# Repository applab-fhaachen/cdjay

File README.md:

# CDjay

## Introduction
The success of Pioneer's CDJ-Players is based on their usability and performance-oriented controls. And while the technology has evolved from CDs over SD-Cards to USB-Keys or direct interaction with a laptop, the control interface itself hasn't changed much. 
Modern CDJs, such as the CDJ-850, CDJ-900, CDJ-2000, and newer offer the possibility to directly connect to a host software, such as Algoriddim DJay, Native Instruments' Traktor, Serato Scratch, in order to be used as controller. 
The goal of this project is to bring this capability to older CDJ-Models in order to keep their control interface. 

## Related Work
A number of other projects have looked at the same idea. Some turning the CDJ into a MIDI-based controller, others integrating a RaspberryPi and running Mixxx, and open source DJ-Software on it, essentially turning them into full-blown, standalone, media-players. 

## About this repository
This repo holds the firmware that turns a Pioneer CDJ-850 into a class-compliant USB controller. It runs on a Raspberry Pi Pico 2 W wired into the CDJ's front-panel button matrix, and it currently:
- Scans the CDJ's S1-S5 / KD0-KD2 button matrix (the display controller drives the S lines; the Pico reads back which K lines go high on each line, see `notes.md` and `include/button/cdj_button.h`) and debounces/queues press-release edges.
- Translates button edges into standard USB-MIDI note on/off messages (`headers/midi_messages.h`) sent over TinyUSB, so any MIDI-capable host (e.g. djay on an iPad) sees the CDJ as a controller.
- Includes a USB-HID descriptor scaffold matching the CDJ-850's own vendor-defined report layout (see `pioneer-800 description.md`) for a future, richer bidirectional mode (LED feedback from the host), though report population is not yet wired up.
- Tracks rotary/jog encoder pulse timing (`include/button/encoder.c`) to derive a speed-scaled MIDI velocity for the search wheel.

Only the Play and Cue buttons are connected end-to-end today (`cdjay.c`); the remaining matrix positions are mapped in `midi_messages.h` but not yet instantiated.

### Hardware
- Raspberry Pi Pico 2 W (`PICO_BOARD pico2_w`), wired to the CDJ-850's S1-S5 (GPIO 10-14) and KD0-KD2 (GPIO 7-9) matrix lines.
- Wiring reference: `image.png` / `notes.md`.

### Building
Requires the Raspberry Pi Pico SDK (v2.2.0) and toolchain, e.g. via the [Pico VS Code extension](https://marketplace.visualstudio.com/items?itemName=raspberry-pi.raspberry-pi-pico) or a manual SDK install pointed to by `PICO_SDK_PATH`.

```sh
mkdir -p build && cd build
cmake ..
make -j4
```

Flash `build/cdjay.uf2` to the Pico by holding BOOTSEL while plugging it in, then copying the file to the mass-storage drive that appears.

### Status
Done:
- Button matrix scanning, debouncing, and edge-queueing (S1-S5 x KD0-KD2).
- USB-MIDI transport via TinyUSB, with a full note-message lookup table for every matrix cell.
- Play and Cue buttons wired end-to-end: press/release -> MIDI note on/off.
- Rotary/jog encoder pulse-interval tracking, mapped to a MIDI-velocity range.
- USB-HID report descriptor matching the real CDJ-850 vendor report layout (not yet populated with live data).

In progress / not yet wired up:
- Remaining buttons (Hold, Time, Track Back/Forward, Eject, Jet, Scratch Back/Forward, Menu/Tag, Zip, Wah) are mapped in `midi_messages.h` and commented out in `cdjay.c`, but not instantiated as `cdj_button_t`s.
- Search/jog encoder velocity is computed (`search_encoder_velocity()`) but not yet fed into a MIDI message.
- `hid_in_report` is never updated from button state, so the HID path currently only sends an all-zero report.
- `tud_hid_set_report_cb` has a TODO for driving the CDJ's own LEDs from host feedback (e.g. Play/Cue LED state from djay).

Roadmap:
1. Instantiate the remaining `create_cdj_button()` calls and confirm each maps to the correct MIDI note against a real CDJ-850.
2. Wire jog/search-wheel velocity into MIDI CC or note messages.
3. Populate `hid_in_report` from button state and enable the HID path as an alternative/parallel transport to MIDI.
4. Implement LED feedback from host HID output reports so the CDJ's own display/LEDs reflect deck state (playing, cued, etc.).
5. Validate end-to-end with djay on iPad (and ideally a second host, e.g. a MIDI-only DAW) for both transports.

## USB-HID
The key is the USB-HID protocol which the newer models provide. Instead of registering as a USB-Midi Device, they have their own, proprietary protocol. While this conflicts with the idea of an open and flexible interface, it has the advantage of providing bi-directional communication, and thus, be able to show additional information directly on the display of the CDJ. The most common DJ software supports the HID protocol.

### Details
Technically, the CDJ registers as a USB device with a number of endpoints:
- The USB-HID interface for the control messages.
- a USB-audio interface for audio-output from the CDJ itself (relevant if you don't use the internal mixer of the software, but an external mixer). 

## Interface
Since we want to focus on interfacing the old CDJs with the modern world (USB-C, Software, etc.), we use iPad mini running Algoriddim's djay in single deck mode, which gives us all the benefits such as touch interaction, integration to streaming services, etc.. Any iPad being able to run djay is fine, although interfacing is easier with the usb-c models. 

### Installation
Install djay from the App-Store on your iPad. Technically, it is possible to run djay from an iPhone, however, it doesn't support single-deck mode on smaller devices. 

### Connecting
If you have an iPad with a lightning-connector, you need a lightning to usb-converter that supports USB OTG. This will make the iPad the host of your USB connection, and the CDJay the client. 
For the USB-Models, just connect the USB-C connection to your iPad. 

## Acknowledgements

This project was supported by...

## License
MIT License

All trademarks are property of their respective owners. This project is part of the education at FH Aachen University of Applied Sciences and not affiliated to any of the brand names.

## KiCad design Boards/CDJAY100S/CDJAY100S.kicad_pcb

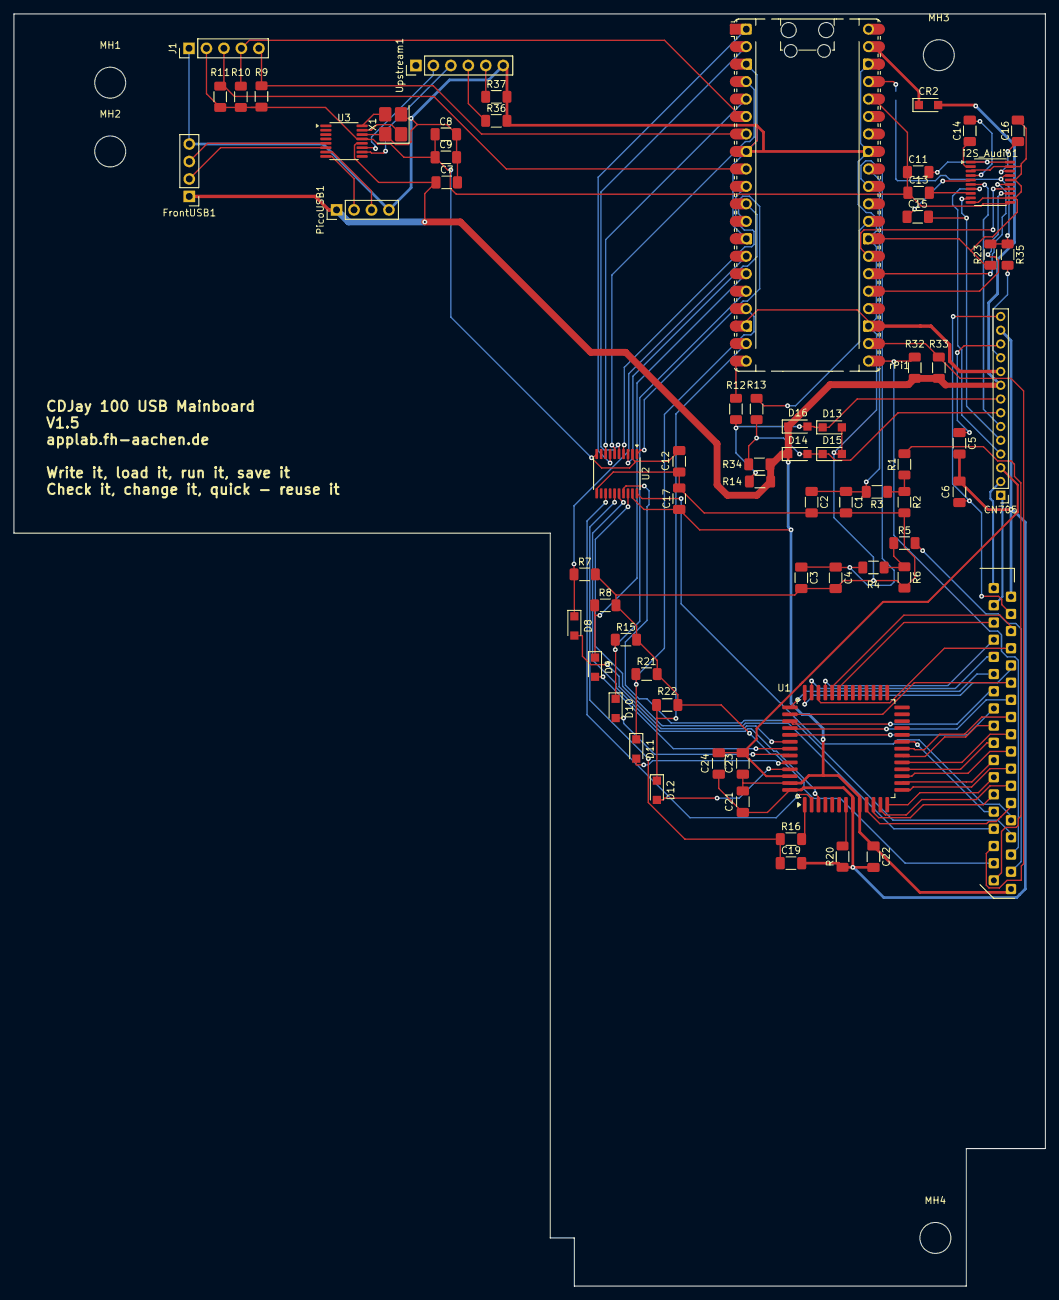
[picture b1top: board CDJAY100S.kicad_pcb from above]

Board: 2 copper layers, 150.0 x 185.0 mm, 74 parts (1 on the bottom side), 98 nets.

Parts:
C1, C4, C11, C12, C13, C17, C21, C22, C23, C24: 100 n; C_1206_3216Metric_Pad1.33x1.80mm_HandSolder
C2, C3: 10 u; C_1206_3216Metric_Pad1.33x1.80mm_HandSolder
C5, C6: 100 u; C_1206_3216Metric_Pad1.33x1.80mm_HandSolder
C7, C8: 10u; C_1206_3216Metric_Pad1.33x1.80mm_HandSolder
C9: 1uf; C_1206_3216Metric_Pad1.33x1.80mm_HandSolder
C14, C15: 2.2 u; C_1206_3216Metric_Pad1.33x1.80mm_HandSolder
C16: 1 u; C_1206_3216Metric_Pad1.33x1.80mm_HandSolder
C19: 100 p; C_1206_3216Metric_Pad1.33x1.80mm_HandSolder
CN701: 52492-3620; ConnectorFPC&FFC_MOL52045-3645-36P_1
CN705: 52151-1410; PinHeader_1x14_P2.00mm_Vertical
CR2: MBR120VLSFT1G; Nexperia_CFP3_SOD-123W
D8, D9, D10, D11, D12, D13, D14, D15, D16: 1SS355VM; Nexperia_CFP3_SOD-123W
FrontUSB1: Conn_01x04_Pin; PinHeader_1x04_P2.54mm_Vertical
J1: Rotary Encoder; PinHeader_1x05_P2.54mm_Vertical
JP1: SolderJumper-2_P1.3mm_Open_Pad1.0x1.5mm
MH1, MH2, MH3, MH4: MountingHole_4.5mm
PicoUSB1: Conn_01x04_Pin; PinHeader_1x04_P2.54mm_Vertical
R1, R5, R9, R10, R11: 10 k; R_1206_3216Metric_Pad1.30x1.75mm_HandSolder
R2, R6: 20 k; R_1206_3216Metric_Pad1.30x1.75mm_HandSolder
R3, R4, R36, R37: 5.1 k; R_1206_3216Metric_Pad1.30x1.75mm_HandSolder
R7, R8, R14, R15, R21, R22, R32, R33, R34, R35: 10k; R_1206_3216Metric_Pad1.30x1.75mm_HandSolder
R12, R13: 2k; R_1206_3216Metric_Pad1.30x1.75mm_HandSolder
R16: 1 k; R_1206_3216Metric_Pad1.30x1.75mm_HandSolder
R20: 82 k; R_1206_3216Metric_Pad1.30x1.75mm_HandSolder
R23: 20k; R_1206_3216Metric_Pad1.30x1.75mm_HandSolder
U1: PT6324Q; QFP-52_14x14mm_P1mm_1
U2: TXS0108EPW; TSSOP-20_4.4x6.5mm_P0.65mm
U3: CH334R; QSOP-16_3.9x4.9mm_P0.635mm
Upstream1: Conn_01x06_Pin; PinHeader_1x06_P2.54mm_Vertical
X1: 12MHz; Crystal_SMD_3225-4Pin_3.2x2.5mm_HandSoldering
i2S_Audio1: PCM5102; TSSOP-20_4.4x6.5mm_P0.65mm
rPi1: RaspberryPi_Pico; RaspberryPi_Pico_Common_Unspecified

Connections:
+3V3: C8.1, C9.1, C11.1, C12.1, C13.1, J1.2 (+), R9.2, R10.1, R11.1, U2.2 (VCCA), U2.10 (OE), U3.13 (VDD33_{LDO}), i2S_Audio1.11 (FLT), rPi1.36 (3V3)
+5V: C7.1, C17.1, C21.1, C22.1, C23.2, CN701.1 (V+5V), CN705.9 (V+5V), CR2.2, D14.1 (K), D16.1 (K), FrontUSB1.1 (VBUS), PicoUSB1.1 (VBUS), R14.2, R32.2, R33.2, R34.2, U1.9 (VDD), U1.51 (VDD), U2.19 (VCCB), U3.12 (V5)
/ADIN: C3.1, C4.1, R4.2, rPi1.31 (GPIO26_ADC0)
/CLK: C19.1, R16.1, U2.15 (B5)
/CT: C1.1, C2.1, R3.2, rPi1.32 (GPIO27_ADC1)
/DIN: U1.2 (DIN), U2.13 (B7)
/JOG1: CN701.5 (JOG1), R32.1, rPi1.21 (GPIO16)
/JOG2: CN701.6 (JOG2), R33.1, rPi1.22 (GPIO17)
/KD0: CN701.9 (KD0), U2.20 (B1)
/SPI0 CS: U2.5 (A4), rPi1.2 (GPIO1)
/SPI0 RX: U2.7 (A6), rPi1.1 (GPIO0)
/SPI0 SCK: U2.6 (A5), rPi1.4 (GPIO2)
/SPI0 TX: U2.8 (A7), rPi1.5 (GPIO3)
/STB: U1.3 (STB), U2.16 (B4)
GND: C1.2, C2.2, C3.2, C4.2, C7.2, C8.2, C9.2, C12.2, C16.2, C17.2, CN701.4 (GNDD), CN705.10 (GNDD), D13.2 (A), D15.2 (A), FrontUSB1.4 (GND), J1.1 (GND), PicoUSB1.4 (GND), R2.2, R6.2, R7.2, R8.2, R15.2, R21.2, R22.1, R23.1, R36.2, R37.2, U2.11 (GND), U3.14 (GND), Upstream1.6 (GND), X1.2 (G), X1.4 (G), i2S_Audio1.3 (CPGND), i2S_Audio1.10 (DEMP), i2S_Audio1.12 (SCK), i2S_Audio1.16 (FMT), i2S_Audio1.19 (DGND), rPi1.3 (GND), rPi1.8 (GND), rPi1.13 (GND), rPi1.18 (GND), rPi1.23 (GND), rPi1.28 (GND), rPi1.33 (AGND), rPi1.38 (GND)
GNDA: C15.2, CN705.5 (GNDA), i2S_Audio1.9 (AGND)
GNDS: C5.2, C6.1, C19.2, C21.2, C22.2, C24.2, CN701.35 (GNDS), CN705.13 (GNDS), R20.1, U1.8 (GND), U1.52 (GND)
unnamed: CN701.36 (AC1), CN705.2 (AC1)
unnamed: CN701.34 (AC2), CN705.1 (AC2)
unnamed: CN701.2 (ADIN), R1.2
unnamed: CN701.3 (CT), R5.2
unnamed: CN701.32 (G1), U1.34 (GR1)
unnamed: CN701.31 (G2), U1.35 (GR2)
unnamed: CN701.30 (G3), U1.36 (GR3)
unnamed: CN701.29 (G4), U1.37 (GR4)
unnamed: CN701.28 (G5), U1.38 (GR5)
unnamed: CN701.27 (G6), U1.39 (GR6)
unnamed: CN701.26 (G7), U1.40 (GR7)
unnamed: CN701.25 (G8), U1.41 (GR8)
unnamed: CN701.24 (G9), U1.42 (GR9)
unnamed: CN701.23 (G10), U1.43 (GR10)
unnamed: CN701.22 (G11), U1.44 (GR11)
unnamed: CN701.8 (KD1), U2.18 (B2)
unnamed: CN701.7 (KD2), U2.17 (B3)
unnamed: CN701.11 (S1), U1.10 (SG1)
unnamed: CN701.12 (S2), U1.11 (SG2)
unnamed: CN701.13 (S3), U1.12 (SG3)
unnamed: CN701.14 (S4), U1.13 (SG4)
unnamed: CN701.15 (S5), U1.14 (SG5)
unnamed: CN701.16 (S6), U1.15 (SG6)
unnamed: CN701.17 (S7), U1.16 (SG7)
unnamed: CN701.18 (S8), U1.17 (SG8)
unnamed: CN701.19 (S9), U1.18 (SG9)
unnamed: CN701.20 (S10), U1.19 (SG10)
unnamed: CN701.21 (S11), U1.20 (SG11)
unnamed: CN701.10 (S12), U1.21 (SG12)
unnamed: CN705.6 (AUDIO_L), i2S_Audio1.6 (OUTL)
unnamed: CN705.4 (AUDIO_R), i2S_Audio1.7 (OUTR)
unnamed: CN705.8 (CONT1), D13.1 (K), D16.2 (A), R12.2, R14.1
unnamed: CN705.7 (CONT2), D14.2 (A), D15.1 (K), R13.2, R34.1
unnamed: CN705.11 (/RST), R35.2
unnamed: D8.2 (A), U1.45 (GR12)
unnamed: D8.1 (K), R7.1, rPi1.14 (GPIO10)
unnamed: D9.2 (A), U1.46 (GR13)
unnamed: D9.1 (K), R8.1, rPi1.15 (GPIO11)
unnamed: D10.2 (A), U1.47 (GR14)
unnamed: D10.1 (K), R15.1, rPi1.16 (GPIO12)
unnamed: D11.2 (A), U1.48 (GR15)
unnamed: D11.1 (K), R21.1, rPi1.17 (GPIO13)
unnamed: D12.2 (A), U1.49 (GR16)
unnamed: D12.1 (K), R22.2, rPi1.19 (GPIO14)
unnamed: FrontUSB1.2 (D+), U3.6 (DP2+)
unnamed: FrontUSB1.3 (D-), U3.5 (DM2-)
unnamed: J1.5 (CLK), R9.1, rPi1.7 (GPIO5)
unnamed: J1.4 (DT), R10.2, rPi1.6 (GPIO4)
unnamed: J1.3 (SW), R11.2, rPi1.9 (GPIO6)
unnamed: JP1.1 (A), rPi1.37 (3V3_EN)
unnamed: JP1.2 (B), R23.2, R35.1, i2S_Audio1.17 (XSMT)
unnamed: PicoUSB1.2 (D+), U3.8 (DP1+)
unnamed: PicoUSB1.3 (D-), U3.7 (DM1-)
unnamed: R1.1, R2.1, R3.1
unnamed: R4.1, R5.1, R6.1
unnamed: R16.2, U1.1 (CLK)
unnamed: R20.2, U1.7 (OSC)
unnamed: U2.1 (A1), rPi1.12 (GPIO9)
unnamed: U2.3 (A2), rPi1.11 (GPIO8)
unnamed: U2.4 (A3), rPi1.10 (GPIO7)
unnamed: U3.10 (DMU-), Upstream1.3 (D-)
unnamed: U3.11 (DPU+), Upstream1.2 (D+)
unnamed: U3.16 (XI), X1.3
unnamed: U3.15 (XO), X1.1
unnamed: R36.1, Upstream1.4 (CC1)
unnamed: R37.1, Upstream1.5 (CC2)
unnamed: C13.2, i2S_Audio1.8 (AVDD)
unnamed: i2S_Audio1.13 (BCK), rPi1.25 (GPIO19)
unnamed: C14.2, i2S_Audio1.4 (CAPM)
unnamed: C14.1, i2S_Audio1.2 (CAPP)
unnamed: C11.2, i2S_Audio1.1 (CPVDD), i2S_Audio1.20 (DVDD)
unnamed: i2S_Audio1.14 (DIN), rPi1.27 (GPIO21)
unnamed: C16.1, i2S_Audio1.18 (LDOO)
unnamed: i2S_Audio1.15 (LRCK), rPi1.26 (GPIO20)
unnamed: C15.1, i2S_Audio1.5 (VNEG)
unnamed: R12.1, rPi1.20 (GPIO15)
unnamed: R13.1, rPi1.29 (GPIO22)
unnamed: CR2.1, rPi1.39 (VSYS)
V+BV: C5.1, CN705.12 (V+BV)
V-BV: C6.2, CN701.33 (V-BV), CN705.14 (V-BV)
Vload: C23.1, C24.1, CN705.3 (VLOAD), U1.50 (VEE)

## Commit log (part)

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2026-04-15 Initial Ideas
2026-04-24 Document the CDJ-100 Board
2026-04-24 More infos on the working principle
2026-04-28 CDJ-850 USB Device Desciptors
2026-05-04 feat: Add initial project structure and implement core functionality for Pico SDK and tinyUSB
2026-05-05 USB Prober Application
2026-05-05 CDJ 800 Analysis
2026-05-05 feat: Update USB descriptors and configuration for MIDI support and product identification
2026-05-07 feat: Implement HID support and update LED control for user input indication
2026-05-07 More details regarding the CDJ-100 Display
2026-05-08 feat: Refactor USB descriptors and implement MIDI support with updated configurations
2026-05-11 feat: Update LED initialization and remove currently unused HID descriptors
2026-05-11 feat: Update MIDI note sequence and add device description for PIONEER CDJ-850 (play/pause)
2026-05-14 feat: Update project configuration and enhance MIDI signal handling with blink
2026-05-19 feat: Enhance LED and button handling for MIDI signal control
2026-05-19 feat: Add initial implementation for MIDI control and LED feedback
2026-05-21 midi message file and array
2026-05-21 feat: Add button debounce library and restructure project structure with lib
2026-05-21 Alle buttons in den arrays
2026-05-22 feat: Implement button handling with callback for play button
2026-06-09 feat: Refactor button callback and update MIDI message handling
2026-06-10 More Info on the Display
2026-06-11 More on the CDJ-100 Implementation idea
2026-06-15 Started a BOM for the CDJ-100
2026-06-15 feat: Add cue button handling and update button initialization
2026-06-16 Figured out how the LEDs work
2026-06-17 More details
2026-06-25 Not speculation anymore
2026-06-30 Initial Commit of Arduino Version
2026-06-30 Compiles and links, yet compatibilitty issues with the USBAudioStream

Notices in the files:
Boards/CDJAY100S/CDJAY100S.kicad_pcb:
CC-By-SA
